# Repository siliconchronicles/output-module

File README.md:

# An 8-bit numeric display

This is a description of a display for showing values of an 8-bit signal. This is useful
for building and debugging breadboard digital circuits working with digital numbers.

It's main features are:

* Can be switched (by a control signal) to display data in both decimal and hex.
* Can interpret data as unsigned numbers (0 to 255), or signed two's complement values (-128 to 127).
  This can also be switched through a control signal.
* has its internal clock, all the input it needs is the input data, power, and mode selection
  lines.

It's inspired in [Ben Eater's output register](https://eater.net/8bit/output), but this
is **just the display** (it does not contain register functionality). I decided to keep
it as a separate unit that I can attach to any register to debug.

[🎥 Video Demo](https://youtube.com/shorts/chPcDeSRnCQ?feature=share)

## Building the display

### Materials

* R1: 1KΩ
* R2: 100KΩ
* R3-R6: 220Ω (you can choose a slightly different value, this controls the brightness)
* C1, C2: 0.01µF (equivalent to 10nF) ceramic. Usually labeled "103"
* U1: LM555 timer IC
* U2: 74HC112 dual J-K flip-flops. This is different than Eater's design that used a 
  74LS76 (obsolete). Other J-K flip-flop ICs will work OK but may have different pin out.
* U3: 74HC139 dual 2:4 decoder
* U4: AT28C64B EEPROM. You'll have to pre-program it (see below)
* U5-U8: 7-segment display, common cathode. For breadboard use look for some with the
  pins at the top+bottom of the digit, and pins at the right spacing.

All ICs should be in DIP package if you're building in breadboards.

You can also choose TTL compatible components (LS or HCT families for the 74 series, and
NE555 for the timer IC). As long as you're consistent, it's the same; all external
inputs come into the EEPROM, which accepts both TTL and CMOS inputs.

### Data sheets

* [LM555](https://www.ti.com/lit/ds/symlink/lmc555.pdf)
* [74HC112](https://www.ti.com/lit/ds/symlink/sn74hc112.pdf)
* [74HC139](https://www.ti.com/lit/ds/symlink/sn74hc139.pdf)
* [AT28C64B](https://ww1.microchip.com/downloads/en/devicedoc/doc0001h.pdf)

## Preparing the ROM

The ROM image is generated by a [Python script](https://github.com/siliconchronicles/output-module/blob/main/mkrom.py). I tried to make it
easy to change. I'm also providing a [pre-built ROM file](output.bin) if you want to use mine unchanged.

You will need an EEPROM programmer to write the ROM. The image generated only uses the lower 4KB (leaving the other 4KB unused). It would
be possible to add other modes there if desired.

The `Config` section has a few settings that you can fiddle with; `FONT` is something you
can change without changing the circuit if you want to provide different selection of
segments or representable values. `ROM_LAYOUT` is used to customize the mapping of
segment to ROM pins; this has been configured for my breadboard layout so that the wires
from ROM to the segment stay in the same side of the breadboard and are tidier.

The `generate_text()` should produce the text representation for an 8-bit value in the
selected mode. `shuffle()` takes care of adjusting the bits described in the font to the
output pin layout selected.

If you set an invalid mode, the display should show `----` (four dashes).

## Possible improvements

* Having one resistor per digit makes the current fixed per digit, which results in symbols
  with many segments (like the digit 8) dimmer than symbols with less segments (like the
  digit 1). It would be better to have resistors in each one of the output lines from the
  ROM, but using a breadboard ends up being a bit tight to do this
* I'm exploring a version where I replace the 112+139 for a single PLA (ATF16V8); that
  would provide a bit of extra physical space for other improvements.

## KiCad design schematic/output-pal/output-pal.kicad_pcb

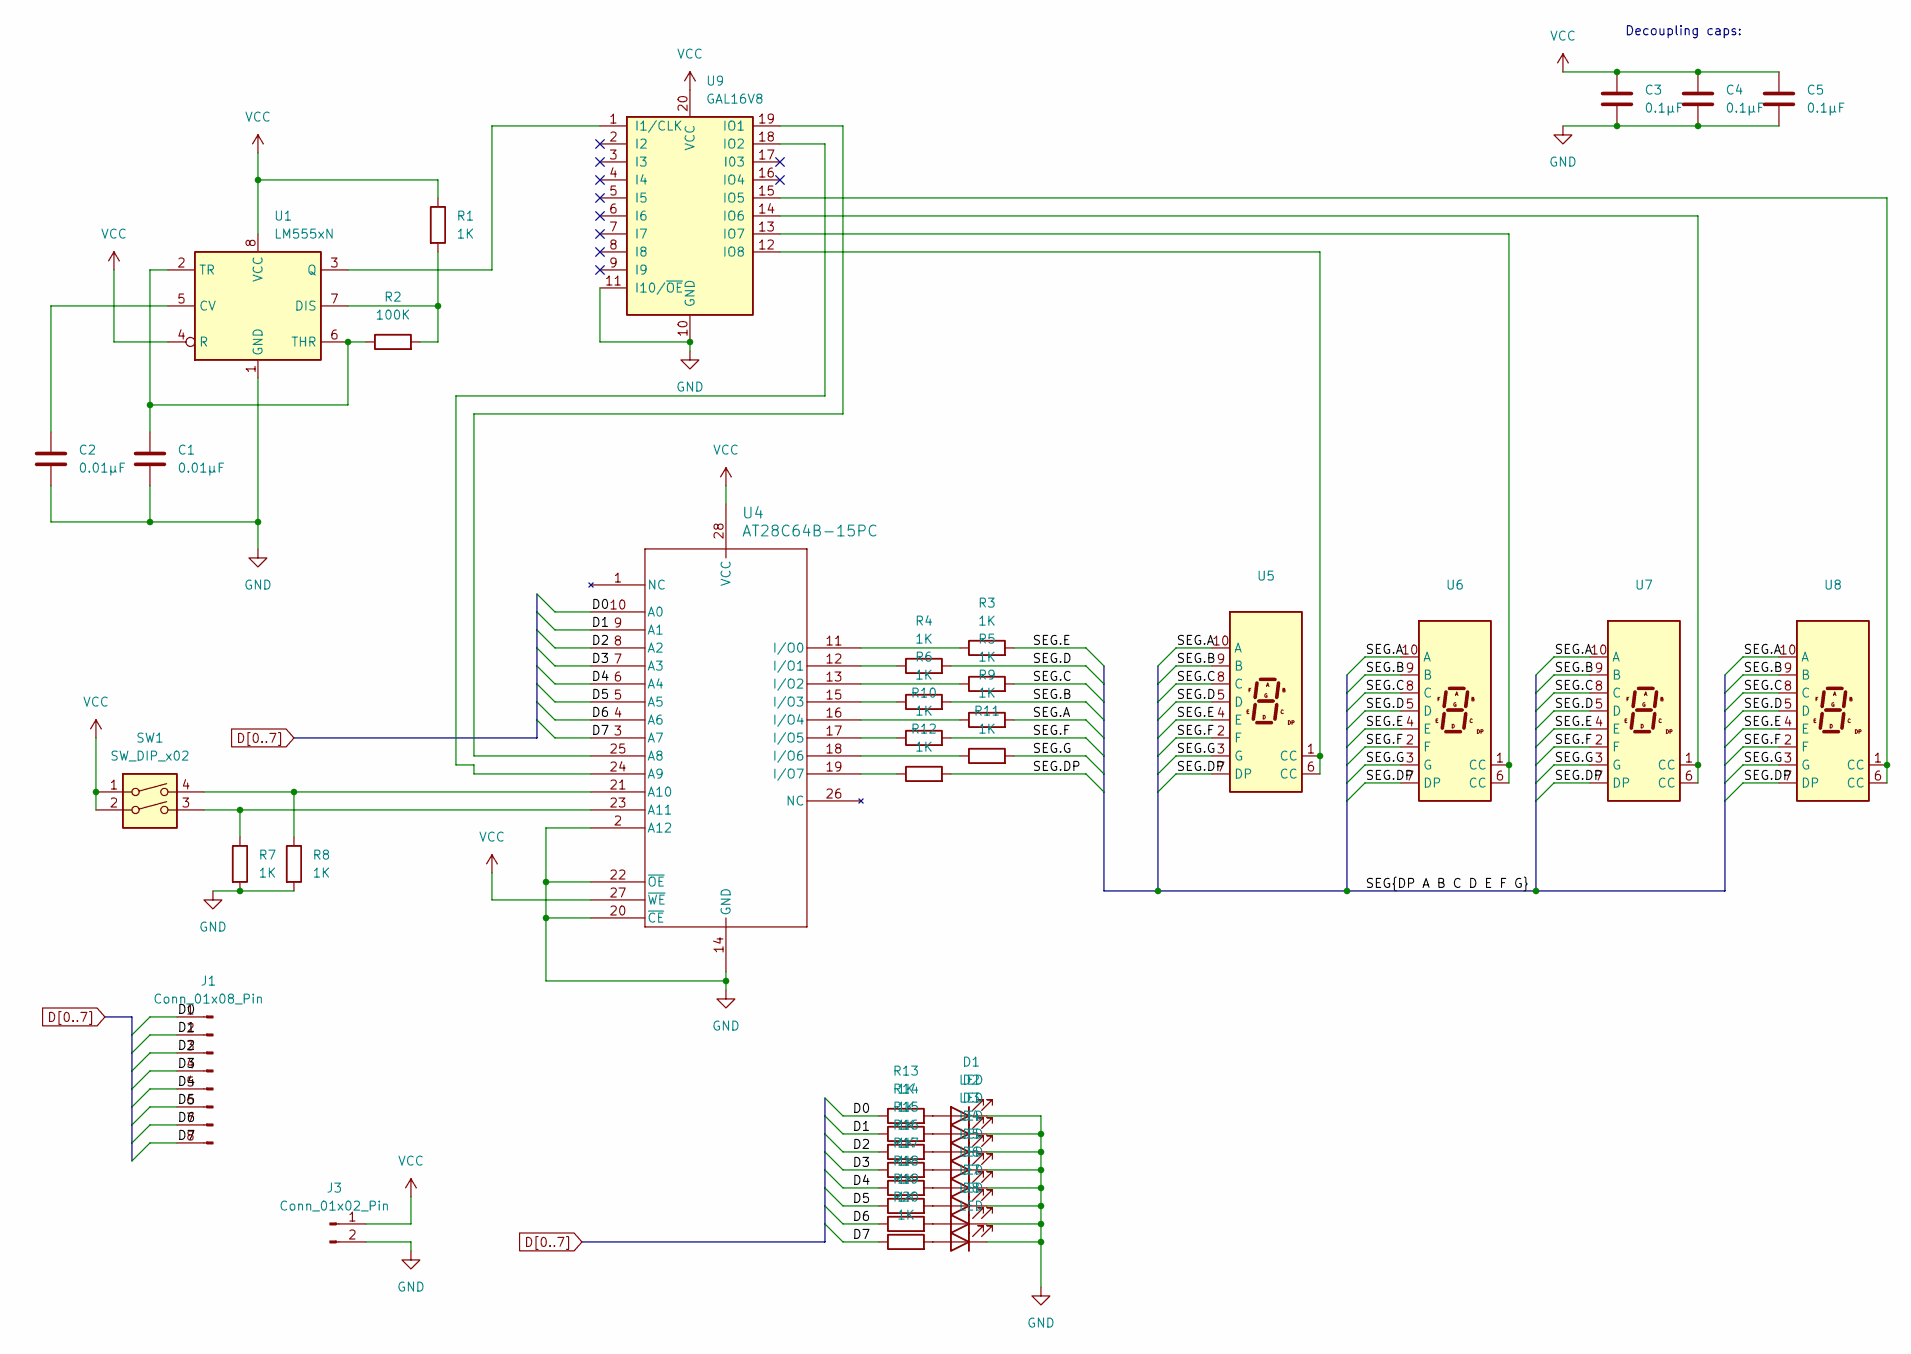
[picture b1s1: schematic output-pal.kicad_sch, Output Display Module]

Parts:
C1, C2: 0.01µF; C_1206_3216Metric_Pad1.33x1.80mm_HandSolder
C3, C4, C5: 0.1µF; C_1206_3216Metric_Pad1.33x1.80mm_HandSolder
D1, D2, D3, D4, D5, D6, D7, D8: LED; C_0805_2012Metric_Pad1.18x1.45mm_HandSolder
J1: Conn_01x08_Pin; PinHeader_1x08_P2.54mm_Vertical
J3: Conn_01x02_Pin; PinHeader_1x02_P2.54mm_Vertical
R1, R3, R4, R5, R6, R7, R8, R9, R10, R11, R12, R13, R14, R15, R16, R17, R18, R19: 1K; R_1206_3216Metric_Pad1.30x1.75mm_HandSolder
R2: 100K; R_1206_3216Metric_Pad1.30x1.75mm_HandSolder
R20: 1K; R_1206_3216Metric
SW1: SW_DIP_x02; SW_DIP_SPSTx02_Piano_10.8x6.64mm_W7.62mm_P2.54mm
U1: LM555xN; SOIC-8_3.9x4.9mm_P1.27mm
U4: AT28C64B-15PC; DIP-28_W15.24mm_Socket
U5, U6, U7, U8: HDSP-7503; 7SegmentLED_generic
U9: GAL16V8; DIP-20_W7.62mm_Socket

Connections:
/SEG.A: R9.2, U5.10 (A), U6.10 (A), U7.10 (A), U8.10 (A)
/SEG.B: R6.2, U5.9 (B), U6.9 (B), U7.9 (B), U8.9 (B)
/SEG.C: R5.2, U5.8 (C), U6.8 (C), U7.8 (C), U8.8 (C)
/SEG.D: R4.2, U5.5 (D), U6.5 (D), U7.5 (D), U8.5 (D)
/SEG.DP: R12.2, U5.7 (DP), U6.7 (DP), U7.7 (DP), U8.7 (DP)
/SEG.E: R3.2, U5.4 (E), U6.4 (E), U7.4 (E), U8.4 (E)
/SEG.F: R10.2, U5.2 (F), U6.2 (F), U7.2 (F), U8.2 (F)
/SEG.G: R11.2, U5.3 (G), U6.3 (G), U7.3 (G), U8.3 (G)
D0: J1.1, R13.1, U4.10 (A0)
D1: J1.2, R14.1, U4.9 (A1)
D2: J1.3, R15.1, U4.8 (A2)
D3: J1.4, R16.1, U4.7 (A3)
D4: J1.5, R17.1, U4.6 (A4)
D5: J1.6, R18.1, U4.5 (A5)
D6: J1.7, R19.1, U4.4 (A6)
D7: J1.8, R20.1, U4.3 (A7)
GND: C1.2, C2.2, C3.2, C4.2, C5.2, D1.1 (K), D2.1 (K), D3.1 (K), D4.1 (K), D5.1 (K), D6.1 (K), D7.1 (K), D8.1 (K), J3.2, R7.2, R8.2, U1.1 (GND), U4.2 (A12), U4.14 (GND), U4.20 (~CE), U4.22 (~OE), U9.10 (GND), U9.11 (I10/~OE)
unnamed: D1.2 (A), R13.2
unnamed: D2.2 (A), R14.2
unnamed: D3.2 (A), R15.2
unnamed: D4.2 (A), R16.2
unnamed: D5.2 (A), R17.2
unnamed: D6.2 (A), R18.2
unnamed: D7.2 (A), R19.2
unnamed: D8.2 (A), R20.2
unnamed: C2.1, U1.5 (CV)
unnamed: R1.2, R2.2, U1.7 (DIS)
unnamed: U1.3 (Q), U9.1 (I1/CLK)
unnamed: C1.1, R2.1, U1.2 (TR), U1.6 (THR)
unnamed: U4.25 (A8), U9.19 (IO1)
unnamed: U4.24 (A9), U9.18 (IO2)
unnamed: R8.1, SW1.4, U4.21 (A10)
unnamed: R7.1, SW1.3, U4.23 (A11)
unnamed: R3.1, U4.11 (I/O0)
unnamed: R4.1, U4.12 (I/O1)
unnamed: R5.1, U4.13 (I/O2)
unnamed: R6.1, U4.15 (I/O3)
unnamed: R9.1, U4.16 (I/O4)
unnamed: R10.1, U4.17 (I/O5)
unnamed: R11.1, U4.18 (I/O6)
unnamed: R12.1, U4.19 (I/O7)
unnamed: U8.1 (CC), U8.6 (CC), U9.15 (IO5)
unnamed: U7.1 (CC), U7.6 (CC), U9.14 (IO6)
unnamed: U6.1 (CC), U6.6 (CC), U9.13 (IO7)
unnamed: U5.1 (CC), U5.6 (CC), U9.12 (IO8)
VCC: C3.1, C4.1, C5.1, J3.1, R1.1, SW1.1, SW1.2, U1.4 (R), U1.8 (VCC), U4.27 (~WE), U4.28 (VCC), U9.20 (VCC)

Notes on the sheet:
Decoupling caps:

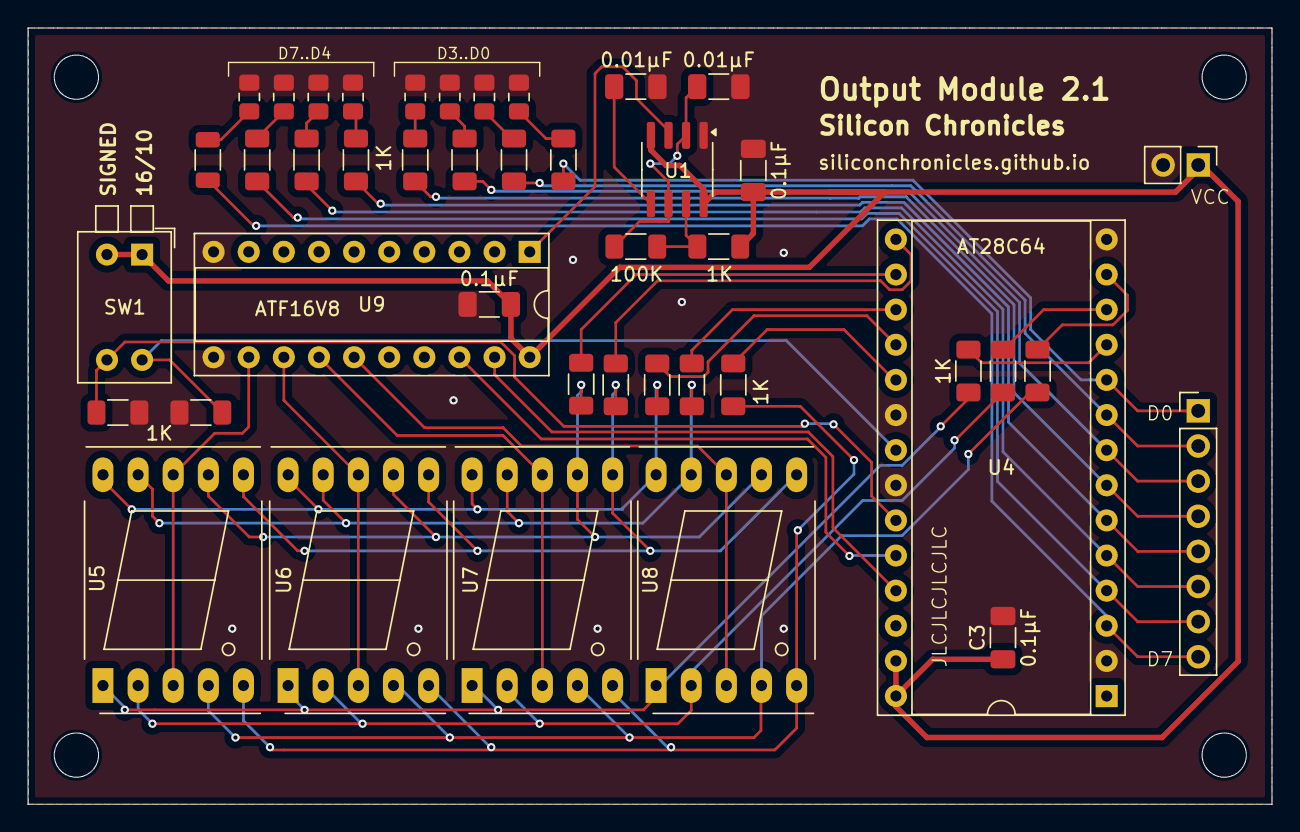
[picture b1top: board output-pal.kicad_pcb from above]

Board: 2 copper layers, 90.0 x 56.1 mm, 43 parts (0 on the bottom side), 46 nets.

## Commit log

2024-05-10 Add rom generator
2024-05-13 Add some documentation
2024-05-13 Add Jekyll config
2024-05-13 Add details about ROM
2024-05-13 Add a few imporvement notes
2024-05-13 Add video link
2024-05-15 Add GA
2024-06-06 Add CUPL file for multiplexer PAL
2024-06-21 Adjust pin order and numbering
2024-06-21 Add Schematic and PCB 2.0
2024-06-23 New release of output.
    Improved layout (more compact)
    Bigger LEDs
    More SMD components (including 7555 and capacitors)
    Front copper fill
2024-07-06 Remapped PIN numbers to final PCB build
